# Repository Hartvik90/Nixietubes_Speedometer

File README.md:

NixieSpeed
==========

MC Speedometer with 3 nixietubes
Adruino stand alone kit

10 bit encoder or GPS reciever

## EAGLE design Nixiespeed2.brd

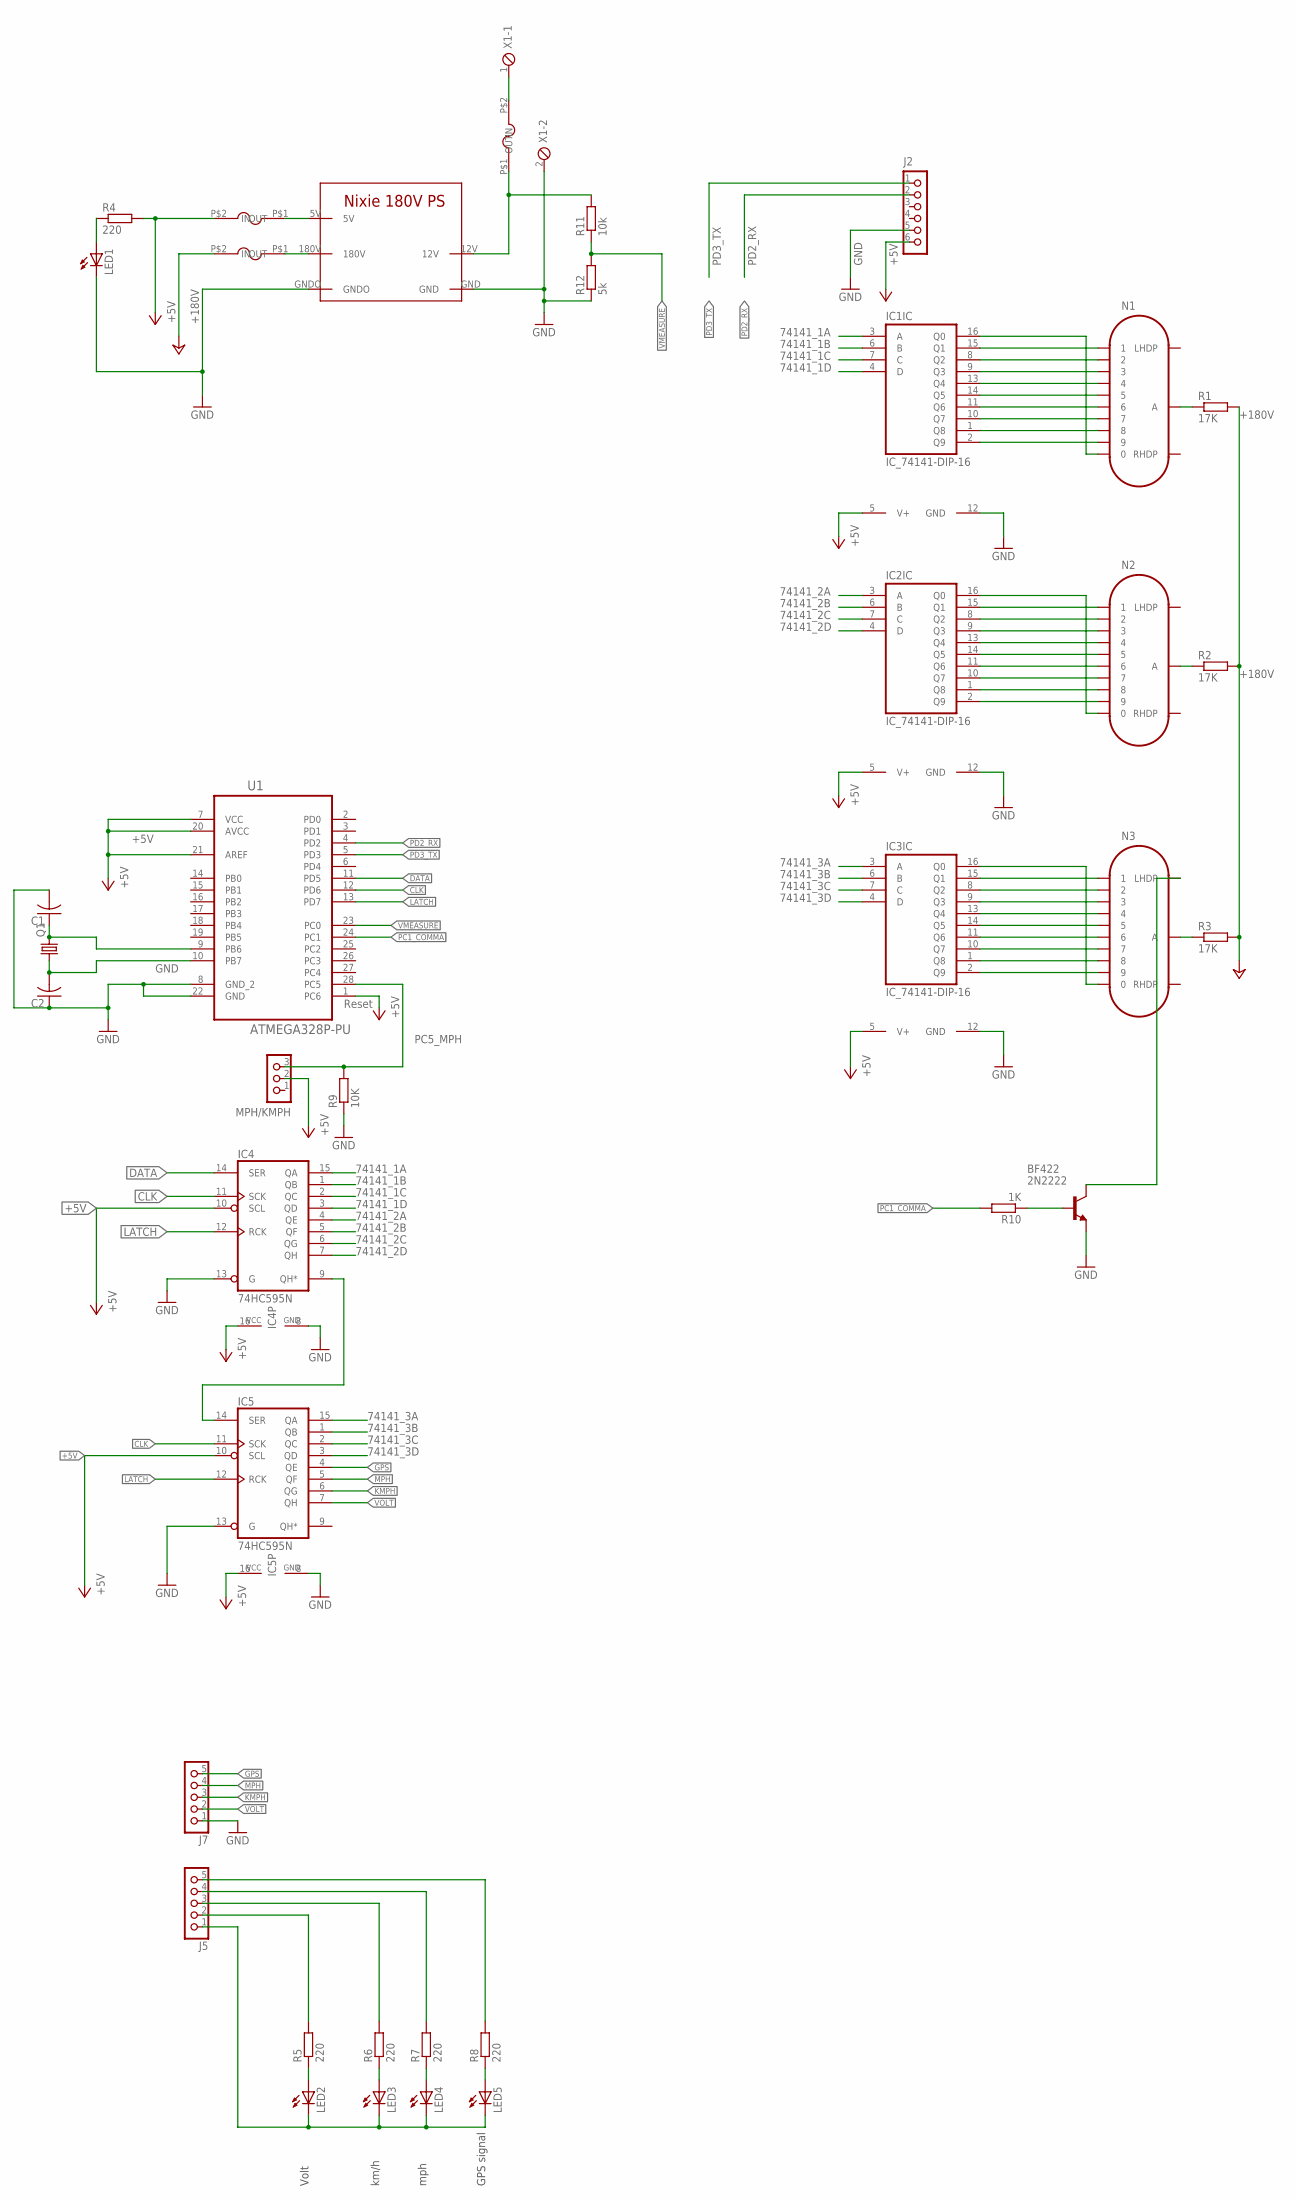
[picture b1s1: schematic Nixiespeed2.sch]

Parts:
BF422: 2N2222; TO92-EBC-OVAL
C1, C2: C-USC1206; C1206
F2, F3: MICROFUSE
IC1, IC2, IC3: IC_74141-DIP-16; DIL16
IC4, IC5: 74HC595N; DIL16
J2: CON_HEADER_1X06-PTH; M1X6
J5, J7: CON_HEADER_1X05-PTH; M1X5
LED1, LED2, LED3, LED4, LED5: LED3MM
MPH/KMPH: CON_HEADER_1X03-PTH; M1X3
N1, N2, N3: IN-14
Q1: CRYSTALHC49S; HC49/S
R1, R2, R3: 17K; 0204/7
R4, R5, R6, R7, R8: 220; M1206
R9: 10K; M1206
R10: 1K; M1206
R11: 10k; M1206
R12: 5k; M1206
U1: ATMEGA328P-PU; DIP254P762X457-28
U$1: NIXIEPS
U$2: MICROFUSE
X1: MPT2; 2POL254

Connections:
12V: R11.2, U$1.12V, U$2.P$1 (IN)
74141_1A: IC1.3 (A), IC4.15 (QA)
74141_1B: IC1.6 (B), IC4.1 (QB)
74141_1C: IC1.7 (C), IC4.2 (QC)
74141_1D: IC1.4 (D), IC4.3 (QD)
74141_2A: IC2.3 (A), IC4.4 (QE)
74141_2B: IC2.6 (B), IC4.5 (QF)
74141_2C: IC2.7 (C), IC4.6 (QG)
74141_2D: IC2.4 (D), IC4.7 (QH)
74141_3A: IC3.3 (A), IC5.15 (QA)
74141_3B: IC3.6 (B), IC5.1 (QB)
74141_3C: IC3.7 (C), IC5.2 (QC)
74141_3D: IC3.4 (D), IC5.3 (QD)
+5V: F2.P$2 (OUT), IC1.5 (V+), IC2.5 (V+), IC3.5 (V+), IC4.10 (SCL), IC4.16 (VCC), IC5.10 (SCL), IC5.16 (VCC), J2.6, MPH/KMPH.2, R4.2, U1.1 (PC6), U1.7 (VCC), U1.20 (AVCC), U1.21 (AREF)
+180V: F3.P$2 (OUT), R1.2, R2.2, R3.2
CLK: IC4.11 (SCK), IC5.11 (SCK), U1.12 (PD6)
DATA: IC4.14 (SER), U1.11 (PD5)
GND: BF422.E, C1.2, C2.1, IC1.12 (GND), IC2.12 (GND), IC3.12 (GND), IC4.8 (GND), IC4.13 (G), IC5.8 (GND), IC5.13 (G), J2.5, J7.1, LED1.K (C), R9.1, R12.1, U1.8 (GND_2), U1.22 (GND), U$1.GND, U$1.GNDO, X1.2
GPS: IC5.4 (QE), J7.5
KMPH: IC5.6 (QG), J7.3
LATCH: IC4.12 (RCK), IC5.12 (RCK), U1.13 (PD7)
MPH: IC5.5 (QF), J7.4
unnamed: IC2.15 (Q1), N2.1
unnamed: IC2.8 (Q2), N2.2
unnamed: IC2.9 (Q3), N2.3
unnamed: IC2.13 (Q4), N2.4
unnamed: IC2.14 (Q5), N2.5
unnamed: IC2.11 (Q6), N2.6
unnamed: IC2.10 (Q7), N2.7
unnamed: IC2.1 (Q8), N2.8
unnamed: IC2.2 (Q9), N2.9
unnamed: IC2.16 (Q0), N2.0
unnamed: IC1.15 (Q1), N1.1
unnamed: IC1.8 (Q2), N1.2
unnamed: IC1.9 (Q3), N1.3
unnamed: IC1.13 (Q4), N1.4
unnamed: IC1.14 (Q5), N1.5
unnamed: IC1.11 (Q6), N1.6
unnamed: IC1.10 (Q7), N1.7
unnamed: IC1.1 (Q8), N1.8
unnamed: IC1.2 (Q9), N1.9
unnamed: IC1.16 (Q0), N1.0
unnamed: IC3.15 (Q1), N3.1
unnamed: IC3.8 (Q2), N3.2
unnamed: IC3.9 (Q3), N3.3
unnamed: IC3.13 (Q4), N3.4
unnamed: IC3.14 (Q5), N3.5
unnamed: IC3.11 (Q6), N3.6
unnamed: IC3.10 (Q7), N3.7
unnamed: IC3.1 (Q8), N3.8
unnamed: IC3.2 (Q9), N3.9
unnamed: IC3.16 (Q0), N3.0
unnamed: N3.A, R3.1
unnamed: N2.A, R2.1
unnamed: N1.A, R1.1
unnamed: LED1.A, R4.1
unnamed: IC4.9 (QH*), IC5.14 (SER)
unnamed: F2.P$1 (IN), U$1.5V
unnamed: BF422.B, R10.1
unnamed: BF422.C, N3.LHDP
unnamed: LED2.A, R5.1
unnamed: J5.2, R5.2
unnamed: J5.3, R6.2
unnamed: J5.4, R7.2
unnamed: LED4.A, R7.1
unnamed: LED3.A, R6.1
unnamed: LED5.A, R8.1
unnamed: J5.5, R8.2
unnamed: J5.1, LED2.K (C), LED3.K (C), LED4.K (C), LED5.K (C)
unnamed: U$2.P$2 (OUT), X1.1
unnamed: C2.2, Q1.1, U1.10 (PB7)
unnamed: C1.1, Q1.2, U1.9 (PB6)
unnamed: F3.P$1 (IN), U$1.180V
PC1_COMMA: R10.2, U1.24 (PC1)
PC5_MPH: MPH/KMPH.3, R9.2, U1.28 (PC5)
PD2_RX: J2.2, U1.4 (PD2)
PD3_TX: J2.1, U1.5 (PD3)
VMEASURE: R11.1, R12.2, U1.23 (PC0)
VOLT: IC5.7 (QH), J7.2

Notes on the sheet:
Volt
km/h
mph
GPS signal
Reset

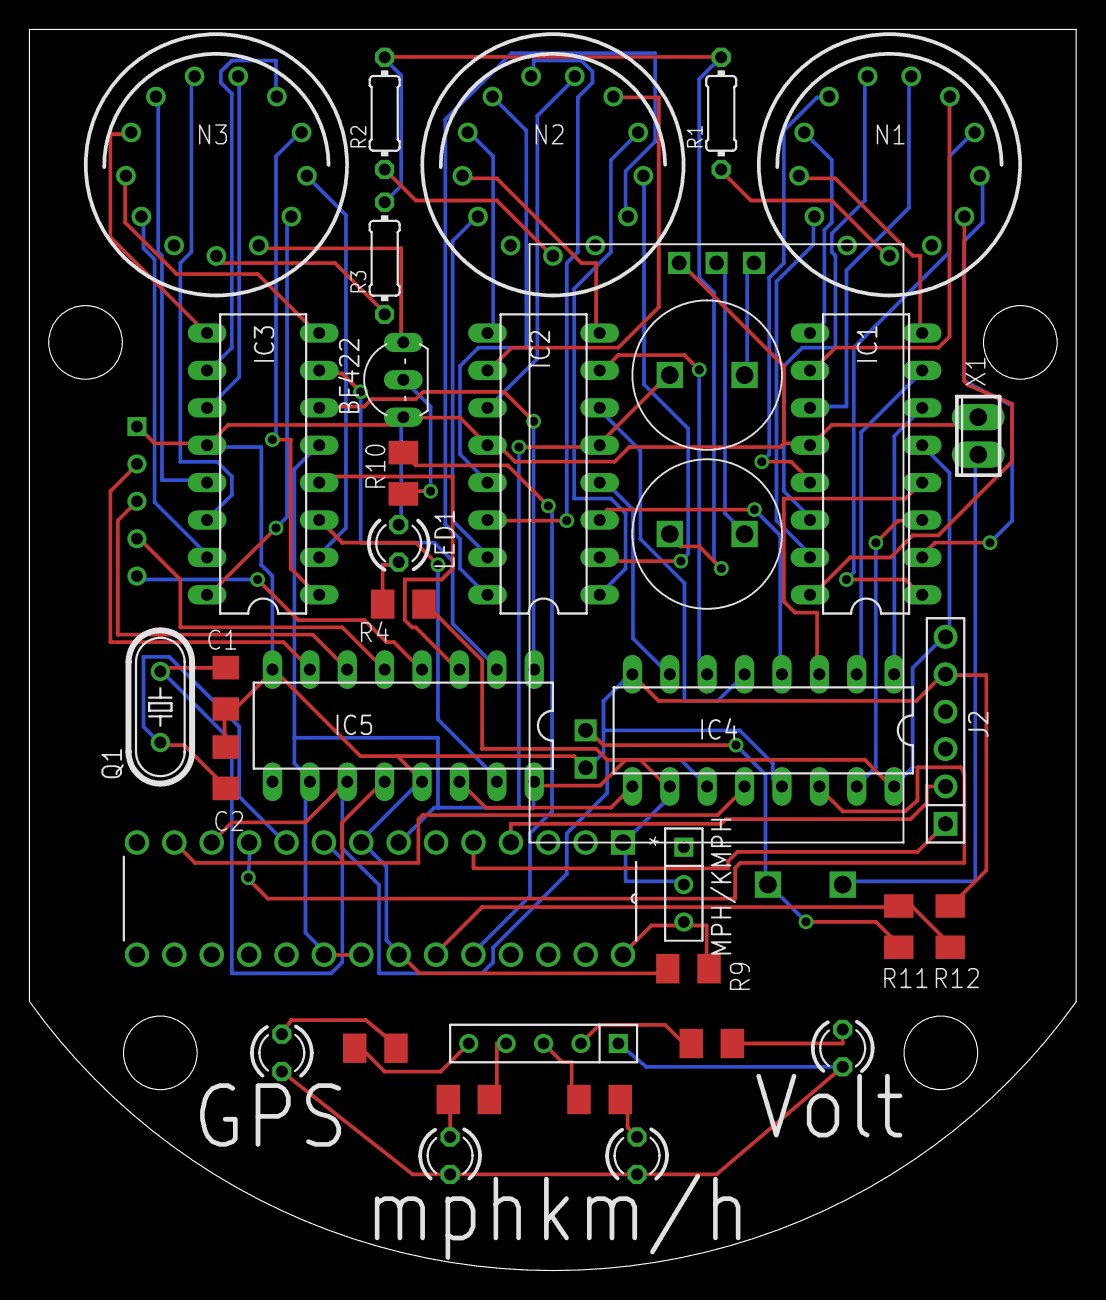
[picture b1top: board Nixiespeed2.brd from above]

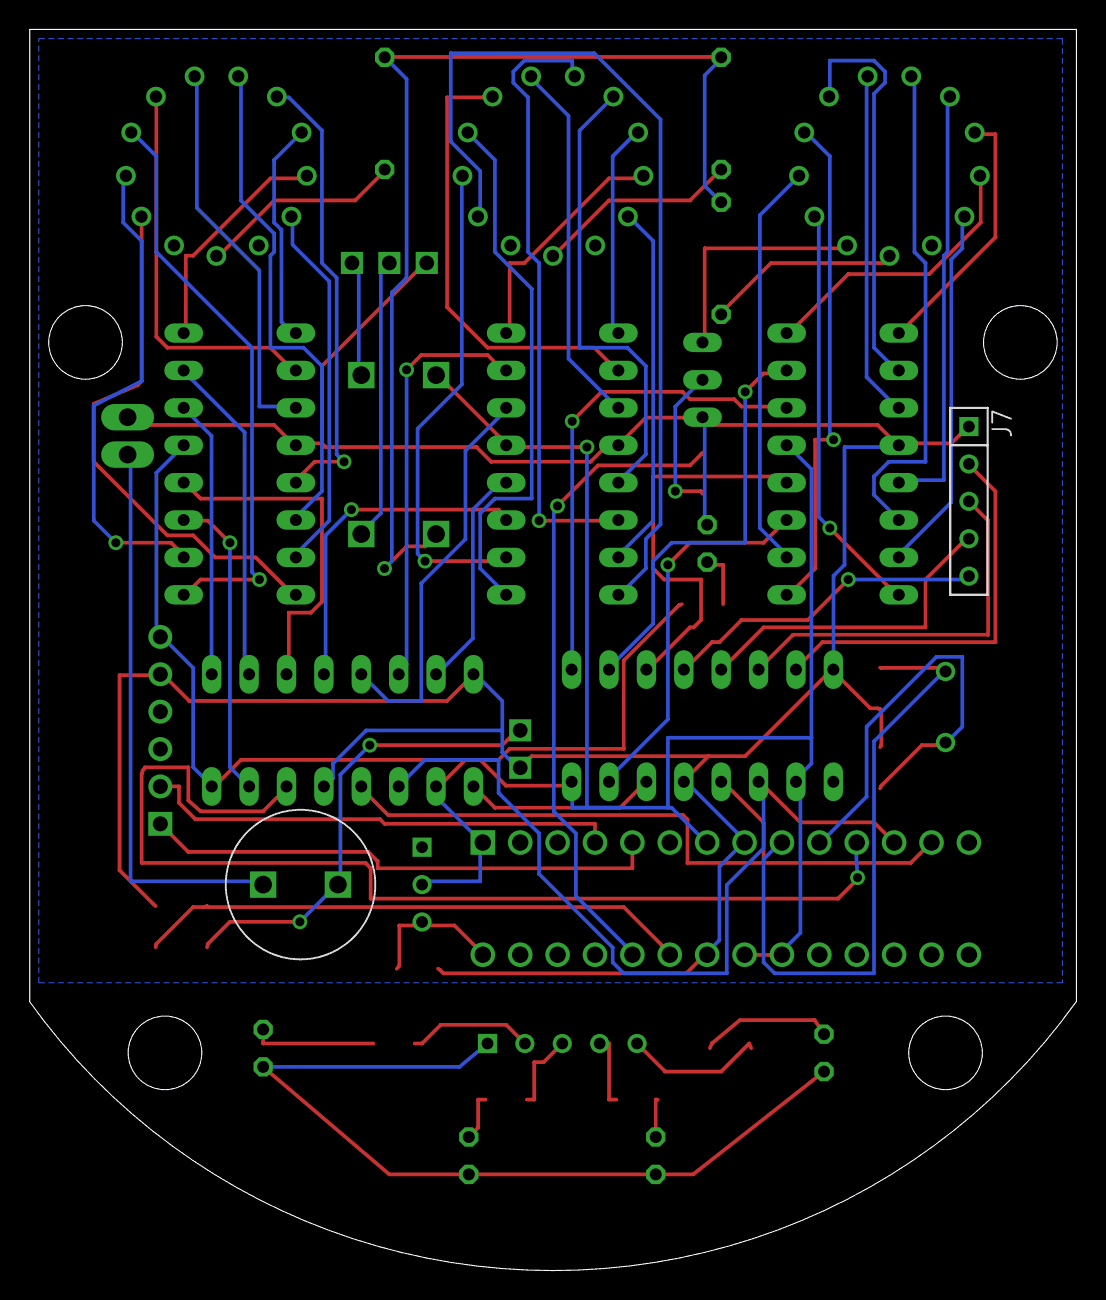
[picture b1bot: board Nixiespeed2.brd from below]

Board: 2 copper layers, 71.1 x 84.3 mm, 39 parts (2 on the bottom side), 79 nets.

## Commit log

2015-02-02 Added the code
2015-02-02 Just editing some.
2015-02-02 Added odometer
    Odometer witch saves to eepro when 12 v supply voltage drops to under 7.
    (Powerloss)
2016-02-04 La til fil!
2016-11-16 GPS support (Initial commit)
2017-02-05 Name edit
2017-02-05 Rename NixieSpeedEncoderino to NixieSpeedEncoder
2017-02-05 Added Eagle files, for PDC (GPS edition)
2017-02-05 Working edition
